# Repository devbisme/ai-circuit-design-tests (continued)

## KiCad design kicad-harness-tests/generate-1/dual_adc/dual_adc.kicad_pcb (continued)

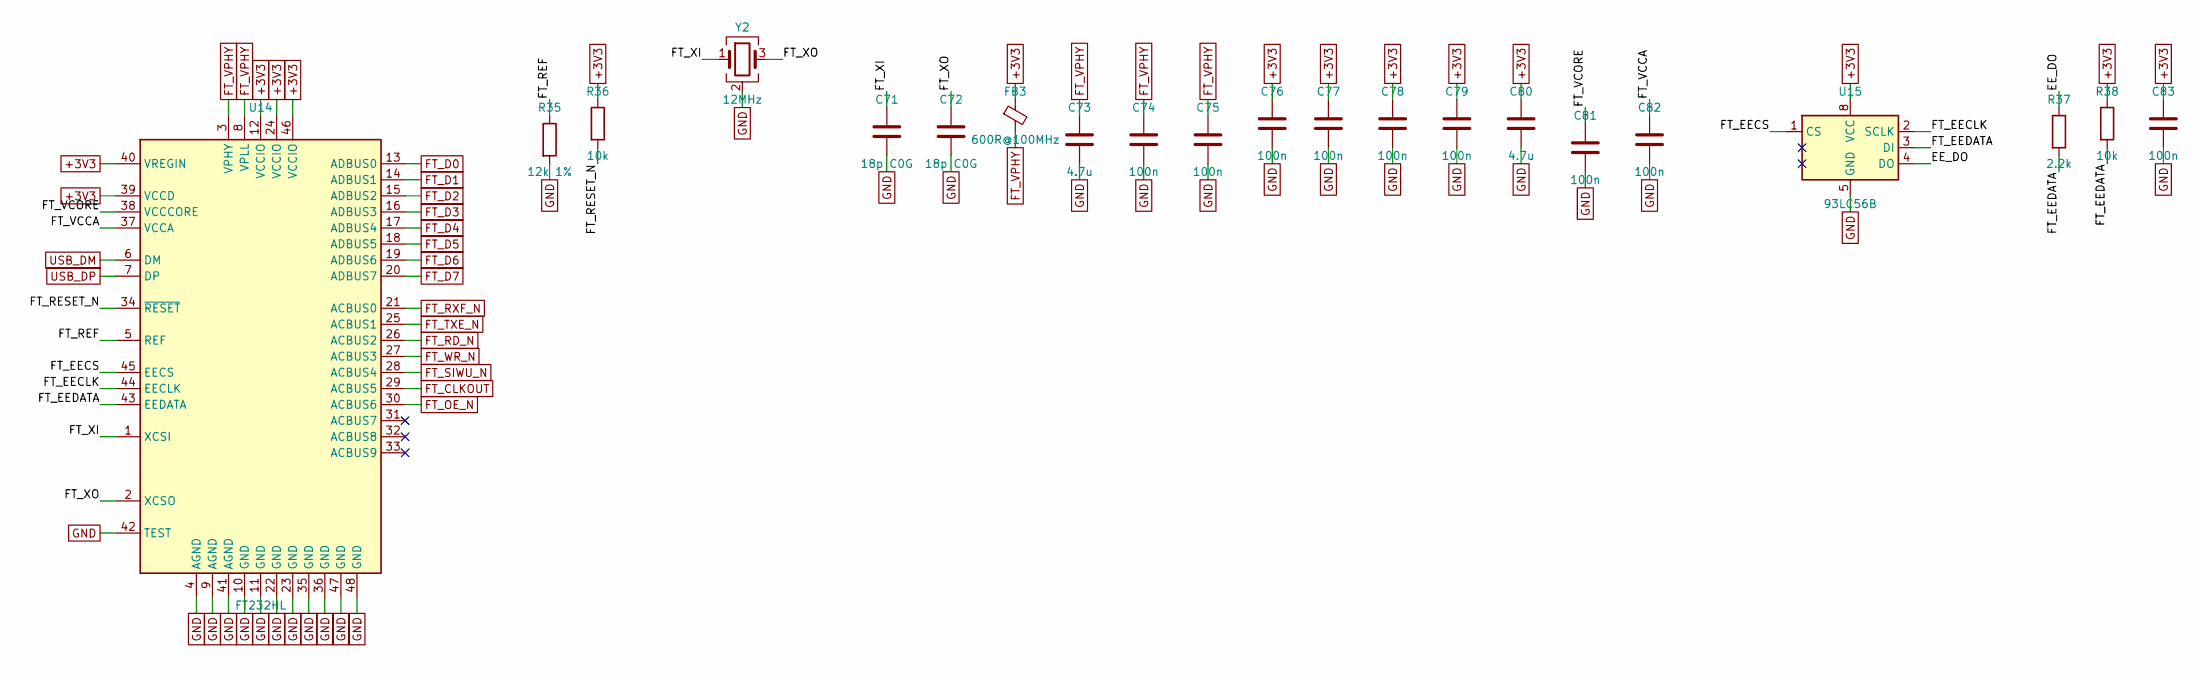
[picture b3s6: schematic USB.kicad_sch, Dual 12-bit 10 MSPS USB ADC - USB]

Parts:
C71, C72: 18p C0G; C_0603_1608Metric
C73, C80: 4.7u; C_0805_2012Metric
C74, C75, C76, C77, C78, C79, C81, C82, C83: 100n; C_0603_1608Metric
FB3: 600R@100MHz; L_0805_2012Metric
R35: 12k 1%; R_0603_1608Metric
R36, R38: 10k; R_0603_1608Metric
R37: 2.2k; R_0603_1608Metric
U14: FT232HL; LQFP-48_7x7mm_P0.5mm
U15: 93LC56B; SOIC-8_3.9x4.9mm_P1.27mm
Y2: 12MHz; Crystal_SMD_3225-4Pin_3.2x2.5mm

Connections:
+3V3: C76.1, C77.1, C78.1, C79.1, C80.1, C83.1, FB3.1, R36.1, R38.1, U14.12 (VCCIO), U14.24 (VCCIO), U14.39 (VCCD), U14.40 (VREGIN), U14.46 (VCCIO), U15.8 (VCC); also elsewhere on the board
/USB/EE_DO: R37.1, U15.4 (DO)
/USB/FT_EECLK: U14.44 (EECLK), U15.2 (SCLK)
/USB/FT_EECS: U14.45 (EECS), U15.1 (CS)
/USB/FT_EEDATA: R37.2, R38.2, U14.43 (EEDATA), U15.3 (DI)
/USB/FT_REF: R35.1, U14.5 (REF)
/USB/FT_RESET_N: R36.2, U14.34 (~RESET)
/USB/FT_VCCA: C82.1, U14.37 (VCCA)
/USB/FT_VCORE: C81.1, U14.38 (VCCCORE)
/USB/FT_XI: C71.1, U14.1 (XCSI), Y2.1
/USB/FT_XO: C72.1, U14.2 (XCSO), Y2.3
FT_CLKOUT: U14.29 (ACBUS5); also elsewhere on the board
FT_D0: U14.13 (ADBUS0); also elsewhere on the board
FT_D1: U14.14 (ADBUS1); also elsewhere on the board
FT_D2: U14.15 (ADBUS2); also elsewhere on the board
FT_D3: U14.16 (ADBUS3); also elsewhere on the board
FT_D4: U14.17 (ADBUS4); also elsewhere on the board
FT_D5: U14.18 (ADBUS5); also elsewhere on the board
FT_D6: U14.19 (ADBUS6); also elsewhere on the board
FT_D7: U14.20 (ADBUS7); also elsewhere on the board
FT_OE_N: U14.30 (ACBUS6); also elsewhere on the board
FT_RD_N: U14.26 (ACBUS2); also elsewhere on the board
FT_RXF_N: U14.21 (ACBUS0); also elsewhere on the board
FT_SIWU_N: U14.28 (ACBUS4); also elsewhere on the board
FT_TXE_N: U14.25 (ACBUS1); also elsewhere on the board
FT_VPHY: C73.1, C74.1, C75.1, FB3.2, U14.3 (VPHY), U14.8 (VPLL)
FT_WR_N: U14.27 (ACBUS3); also elsewhere on the board
GND: C71.2, C72.2, C73.2, C74.2, C75.2, C76.2, C77.2, C78.2, C79.2, C80.2, C81.2, C82.2, C83.2, R35.2, U14.4 (AGND), U14.9 (AGND), U14.10 (GND), U14.11 (GND), U14.22 (GND), U14.23 (GND), U14.35 (GND), U14.36 (GND), U14.41 (AGND), U14.42 (TEST), U14.47 (GND), U14.48 (GND), U15.5 (GND), Y2.2 (G), Y2.4 (G); also elsewhere on the board
USB_DM: U14.6 (DM); also elsewhere on the board
USB_DP: U14.7 (DP); also elsewhere on the board

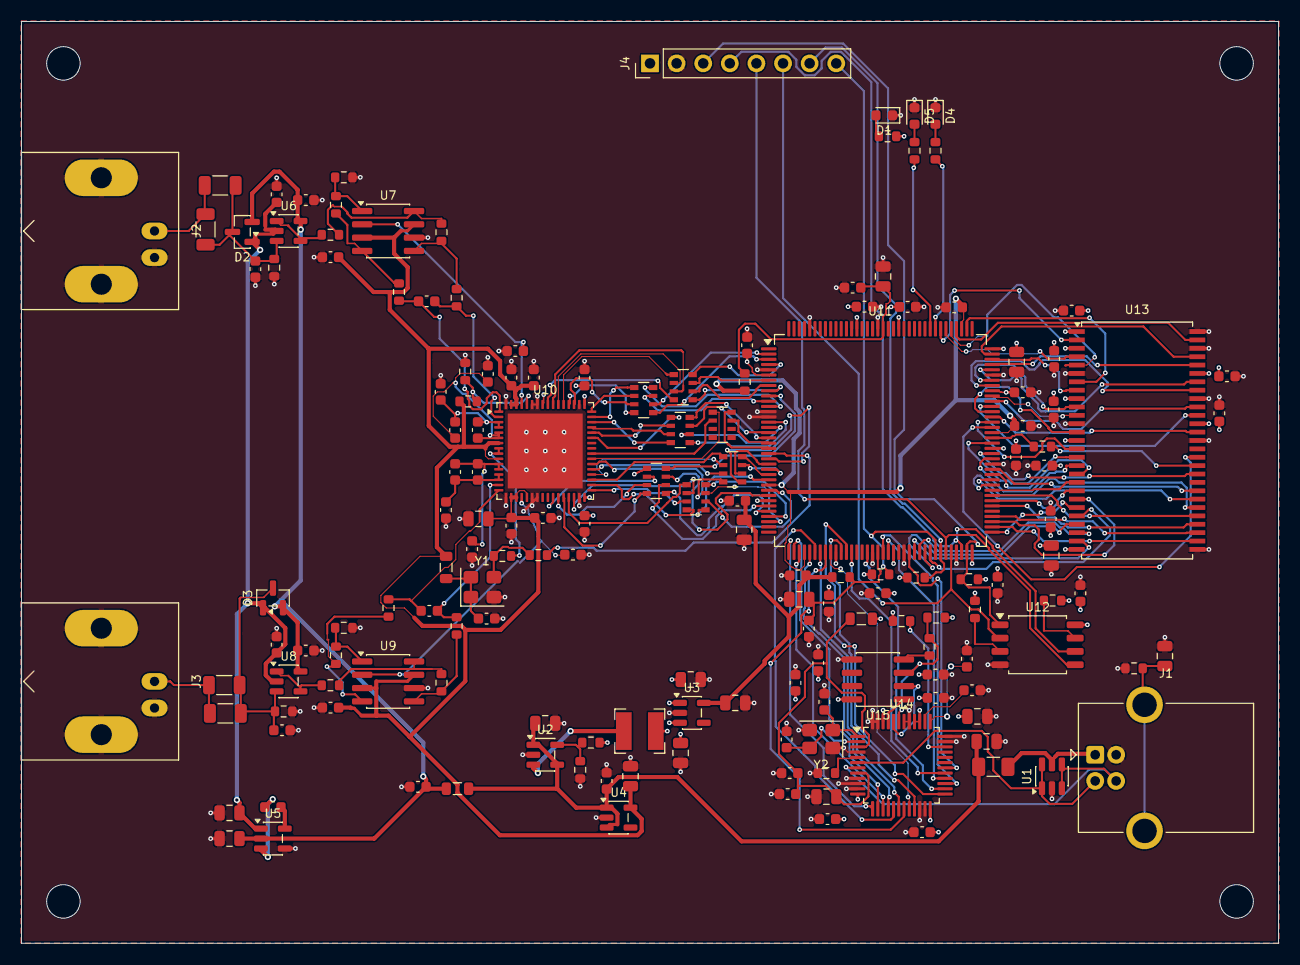
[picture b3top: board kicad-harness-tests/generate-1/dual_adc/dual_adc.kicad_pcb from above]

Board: 4 copper layers, 120.0 x 88.0 mm, 163 parts (0 on the bottom side), 176 nets.

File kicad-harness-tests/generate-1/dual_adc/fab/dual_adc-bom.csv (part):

"Refs","Value","Footprint","Qty","DNP"
"C1","4.7n","Capacitor_SMD:C_0805_2012Metric","1",""
"C2","10u","Capacitor_SMD:C_0805_2012Metric","1",""
"C3","10u","Capacitor_SMD:C_0805_2012Metric","1",""
"C4","22u","Capacitor_SMD:C_0805_2012Metric","1",""
"C5","22u","Capacitor_SMD:C_0805_2012Metric","1",""
"C6","1u","Capacitor_SMD:C_0603_1608Metric","1",""
"C7","10u","Capacitor_SMD:C_0805_2012Metric","1",""
"C8","1u","Capacitor_SMD:C_0603_1608Metric","1",""
"C9","10u","Capacitor_SMD:C_0805_2012Metric","1",""
"C10","10u","Capacitor_SMD:C_0805_2012Metric","1",""
"C11","1u","Capacitor_SMD:C_0603_1608Metric","1",""
"C12","1u","Capacitor_SMD:C_0603_1608Metric","1",""
"C13","4.7u","Capacitor_SMD:C_0805_2012Metric","1",""
"C14","16p C0G","Capacitor_SMD:C_1206_3216Metric","1",""
"C15","150p C0G","Capacitor_SMD:C_0603_1608Metric","1",""
"C16","100n","Capacitor_SMD:C_0603_1608Metric","1",""
"C17","100n","Capacitor_SMD:C_0603_1608Metric","1",""
"C18","100n","Capacitor_SMD:C_0603_1608Metric","1",""
"C19","330p C0G","Capacitor_SMD:C_0603_1608Metric","1",""
"C20","16p C0G","Capacitor_SMD:C_1206_3216Metric","1",""
"C21","150p C0G","Capacitor_SMD:C_0603_1608Metric","1",""
"C22","100n","Capacitor_SMD:C_0603_1608Metric","1",""
"C23","100n","Capacitor_SMD:C_0603_1608Metric","1",""
"C24","100n","Capacitor_SMD:C_0603_1608Metric","1",""
"C25","330p C0G","Capacitor_SMD:C_0603_1608Metric","1",""
"C26","100n","Capacitor_SMD:C_0603_1608Metric","1",""
"C27","100n","Capacitor_SMD:C_0603_1608Metric","1",""
"C28","100n","Capacitor_SMD:C_0603_1608Metric","1",""
"C29","100n","Capacitor_SMD:C_0603_1608Metric","1",""
"C30","10u","Capacitor_SMD:C_0805_2012Metric","1",""
"C31","100n","Capacitor_SMD:C_0603_1608Metric","1",""
"C32","100n","Capacitor_SMD:C_0603_1608Metric","1",""
"C33","100n","Capacitor_SMD:C_0603_1608Metric","1",""
"C34","2.2u","Capacitor_SMD:C_0603_1608Metric","1",""
"C35","1u","Capacitor_SMD:C_0603_1608Metric","1",""
"C36","1u","Capacitor_SMD:C_0603_1608Metric","1",""
"C37","2.2u","Capacitor_SMD:C_0603_1608Metric","1",""
"C38","100n","Capacitor_SMD:C_0603_1608Metric","1",""
"C39","2.2u","Capacitor_SMD:C_0603_1608Metric","1",""
"C40","1u","Capacitor_SMD:C_0603_1608Metric","1",""
"C41","1u","Capacitor_SMD:C_0603_1608Metric","1",""
"C42","2.2u","Capacitor_SMD:C_0603_1608Metric","1",""
"C43","100n","Capacitor_SMD:C_0603_1608Metric","1",""
"C44","100n","Capacitor_SMD:C_0603_1608Metric","1",""
"C45","100n","Capacitor_SMD:C_0603_1608Metric","1",""
"C46","100n","Capacitor_SMD:C_0603_1608Metric","1",""
"C47","100n","Capacitor_SMD:C_0603_1608Metric","1",""
"C48","10u","Capacitor_SMD:C_0805_2012Metric","1",""
"C49","100n","Capacitor_SMD:C_0603_1608Metric","1",""
"C50","100n","Capacitor_SMD:C_0603_1608Metric","1",""
"C51","100n","Capacitor_SMD:C_0603_1608Metric","1",""
"C52","100n","Capacitor_SMD:C_0603_1608Metric","1",""
"C53","100n","Capacitor_SMD:C_0603_1608Metric","1",""
"C54","100n","Capacitor_SMD:C_0603_1608Metric","1",""
"C55","100n","Capacitor_SMD:C_0603_1608Metric","1",""
"C56","100n","Capacitor_SMD:C_0603_1608Metric","1",""
"C57","10u","Capacitor_SMD:C_0805_2012Metric","1",""
"C58","10u","Capacitor_SMD:C_0805_2012Metric","1",""
"C59","100n","Capacitor_SMD:C_0603_1608Metric","1",""
"C60","10u","Capacitor_SMD:C_0805_2012Metric","1",""
"C61","100n","Capacitor_SMD:C_0603_1608Metric","1",""
"C62","100n","Capacitor_SMD:C_0603_1608Metric","1",""
"C63","100n","Capacitor_SMD:C_0603_1608Metric","1",""
"C64","100n","Capacitor_SMD:C_0603_1608Metric","1",""
"C65","100n","Capacitor_SMD:C_0603_1608Metric","1",""
"C66","100n","Capacitor_SMD:C_0603_1608Metric","1",""
"C67","100n","Capacitor_SMD:C_0603_1608Metric","1",""
"C68","100n","Capacitor_SMD:C_0603_1608Metric","1",""
"C69","100n","Capacitor_SMD:C_0603_1608Metric","1",""
"C70","10u","Capacitor_SMD:C_0805_2012Metric","1",""
"C71","18p C0G","Capacitor_SMD:C_0603_1608Metric","1",""
"C72","18p C0G","Capacitor_SMD:C_0603_1608Metric","1",""
"C73","4.7u","Capacitor_SMD:C_0805_2012Metric","1",""
"C74","100n","Capacitor_SMD:C_0603_1608Metric","1",""
"C75","100n","Capacitor_SMD:C_0603_1608Metric","1",""
"C76","100n","Capacitor_SMD:C_0603_1608Metric","1",""
"C77","100n","Capacitor_SMD:C_0603_1608Metric","1",""
"C78","100n","Capacitor_SMD:C_0603_1608Metric","1",""
"C79","100n","Capacitor_SMD:C_0603_1608Metric","1",""
"C80","4.7u","Capacitor_SMD:C_0805_2012Metric","1",""
"C81","100n","Capacitor_SMD:C_0603_1608Metric","1",""
"C82","100n","Capacitor_SMD:C_0603_1608Metric","1",""
"C83","100n","Capacitor_SMD:C_0603_1608Metric","1",""
"D1","green","LED_SMD:LED_0603_1608Metric","1",""
"D2","BAV99","Package_TO_SOT_SMD:SOT-23","1",""
"D3","BAV99","Package_TO_SOT_SMD:SOT-23","1",""
"D4","yellow","LED_SMD:LED_0603_1608Metric","1",""
"D5","yellow","LED_SMD:LED_0603_1608Metric","1",""
"F1","750mA hold","Fuse:Fuse_1206_3216Metric","1",""
"FB1","600R@100MHz","Inductor_SMD:L_0805_2012Metric","1",""
"FB2","600R@100MHz","Inductor_SMD:L_0805_2012Metric","1",""
"FB3","600R@100MHz","Inductor_SMD:L_0805_2012Metric","1",""
"H1","MountingHole","MountingHole:MountingHole_3.2mm_M3","1",""
"H2","MountingHole","MountingHole:MountingHole_3.2mm_M3","1",""
"H3","MountingHole","MountingHole:MountingHole_3.2mm_M3","1",""
"H4","MountingHole","MountingHole:MountingHole_3.2mm_M3","1",""
"J1","USB_B","Connector_USB:USB_B_OST_USB-B1HSxx_Horizontal","1",""
"J2","BNC_CHA","Connector_Coaxial:BNC_Amphenol_B6252HB-NPP3G-50_Horizontal","1",""
"J3","BNC_CHB","Connector_Coaxial:BNC_Amphenol_B6252HB-NPP3G-50_Horizontal","1",""
"J4","PROG","Connector_PinHeader_2.54mm:PinHeader_1x08_P2.54mm_Vertical","1",""
"L1","2.2u","Inductor_SMD:L_Bourns-SRN4018","1",""
"R1","1M","Resistor_SMD:R_0603_1608Metric","1",""
"R2","100k","Resistor_SMD:R_0603_1608Metric","1",""
"R3","22.1k","Resistor_SMD:R_0603_1608Metric","1",""
"R4","1k","Resistor_SMD:R_0603_1608Metric","1",""
"R5","909k","Resistor_SMD:R_1206_3216Metric","1",""
"R6","100k","Resistor_SMD:R_0603_1608Metric","1",""
"R7","1k","Resistor_SMD:R_0603_1608Metric","1",""
"R8","1k","Resistor_SMD:R_0603_1608Metric","1",""
"R9","953","Resistor_SMD:R_0603_1608Metric","1",""
"R10","953","Resistor_SMD:R_0603_1608Metric","1",""
"R11","49.9","Resistor_SMD:R_0603_1608Metric","1",""
"R12","49.9","Resistor_SMD:R_0603_1608Metric","1",""
"R13","909k","Resistor_SMD:R_1206_3216Metric","1",""
"R14","100k","Resistor_SMD:R_0603_1608Metric","1",""
"R15","1k","Resistor_SMD:R_0603_1608Metric","1",""
"R16","1k","Resistor_SMD:R_0603_1608Metric","1",""
"R17","953","Resistor_SMD:R_0603_1608Metric","1",""
"R18","953","Resistor_SMD:R_0603_1608Metric","1",""
"R19","49.9","Resistor_SMD:R_0603_1608Metric","1",""
"R20","49.9","Resistor_SMD:R_0603_1608Metric","1",""
"R21","10k","Resistor_SMD:R_0603_1608Metric","1",""
"R22","20k","Resistor_SMD:R_0603_1608Metric","1",""
"R23","33","Resistor_SMD:R_0603_1608Metric","1",""
"R24","33","Resistor_SMD:R_0603_1608Metric","1",""
"R25","100","Resistor_SMD:R_0603_1608Metric","1",""
"R26","100","Resistor_SMD:R_0603_1608Metric","1",""
"R27","10k","Resistor_SMD:R_0603_1608Metric","1",""
"R28","10k","Resistor_SMD:R_0603_1608Metric","1",""
"R29","10k","Resistor_SMD:R_0603_1608Metric","1",""
"R30","10k","Resistor_SMD:R_0603_1608Metric","1",""
"R31","10k","Resistor_SMD:R_0603_1608Metric","1",""
"R32","1k","Resistor_SMD:R_0603_1608Metric","1",""
"R33","1k","Resistor_SMD:R_0603_1608Metric","1",""
"R34","22","Resistor_SMD:R_0603_1608Metric","1",""
"R35","12k 1%","Resistor_SMD:R_0603_1608Metric","1",""
"R36","10k","Resistor_SMD:R_0603_1608Metric","1",""
"R37","2.2k","Resistor_SMD:R_0603_1608Metric","1",""
"R38","10k","Resistor_SMD:R_0603_1608Metric","1",""
"RN1","4x33","Resistor_SMD:R_Array_Convex_4x0603","1",""
"RN2","4x33","Resistor_SMD:R_Array_Convex_4x0603","1",""
"RN3","4x33","Resistor_SMD:R_Array_Convex_4x0603","1",""
"RN4","4x33","Resistor_SMD:R_Array_Convex_4x0603","1",""
"RN5","4x33","Resistor_SMD:R_Array_Convex_4x0603","1",""
"RN6","4x33","Resistor_SMD:R_Array_Convex_4x0603","1",""
"RN7","4x33","Resistor_SMD:R_Array_Convex_4x0603","1",""
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
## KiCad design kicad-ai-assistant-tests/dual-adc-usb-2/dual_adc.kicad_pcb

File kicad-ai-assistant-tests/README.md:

# KiCad-AI-Assistant — tests

## Tool under test

[KiCad-AI-Assistant](https://github.com/paul356/KiCad-AI-Assistant) has two parts:

- **A KiCad action plugin.** It is a chat panel in the PCB editor with its own agent loop and a
  Freerouting integration.
- **An MCP server, `kcaa`.** It runs standalone with the "full" profile and registers 129
  tools for:
  - Schematic editing: symbol search and placement, wires, labels, no-connects, sheets and
    sheet pins, properties, symbol and library creation, group placement.
  - Schematic analysis: netlist extraction, ERC through `kicad-cli`, circuit-pattern
    recognition, BOM analysis, validation.
  - PCB editing: footprint search and placement, alignment and distribution, flipping,
    groups, board outline, zones, net classes and design rules.
  - Routing: a pad-to-pad push-and-shove router, vias, a ratsnest query, and a pure-Python
    board renderer.
  - Live-KiCad (IPC) actions: update the PCB from the schematic, refill zones, save, reload,
    and open the DRC dialog.
  - Twelve Markdown "skills" with workflow guidance.

Claude Code used only the MCP server; the plugin's chat panel was not used. Schematic tools edit
`.kicad_sch` files directly (via `kicad-skip`); the IPC tools need the KiCad GUI open with its
API server enabled. Installation is described in [`setup.md`](setup.md).

The tool is a hybrid (both analyzer and generator), so it was tested in both roles, like
[kicad-mcp-server](../kicad-mcp-server-tests/), [kicad-mcp-pro](../kicad-mcp-pro-tests/) and
[eda-agent](../eda-agent-tests/).

- **Version:** kcaa 0.2.7 from PyPI. Plugin files are from the repo at commit ce4161f
  (2026-10-09).
- **Profile:** `full` (standalone MCP server, stdio).
- **Model:** Claude Opus 5.5 on a Claude Pro plan, Claude Code v2.1.296 (both runs).
- **Backend:** KiCad 10.0.4 (`~/bin/kicad10-root`: `kicad-cli`, pcbnew Python, and the GUI for
  IPC). Run 2 also used Freerouting 2.4.1.

## Why this tool

- It is one of the few KiCad MCP servers with tools for both schematic capture **and** PCB
  work: placement, zones, rules and its own router.
- It ships workflow skills and a placement scorer, which suggest it is aimed at building
  designs, not only inspecting them.

## Runs

| Run | What it tests | Prompts | Outcome | Equiv. API cost | Time |
|---|---|---|---|---|---|
| [`dual-adc-usb-1`](dual-adc-usb-1/) | **Analysis** and JLCPCB fab outputs for an existing design | 1 (multi-part, [`analysis_prompt.txt`](dual-adc-usb-1/analysis_prompt.txt)) | ERC 0 errors, DRC 0 errors; 18 ranked findings; Gerbers, BOM, CPL, PNG. Most of the review came from fallbacks because kcaa's analysis tools failed on this design | $3.71 | ~20 min |
| [`dual-adc-usb-2`](dual-adc-usb-2/) | A **full design**, from requirements to Gerbers | 1, plus "keep going" after a usage-limit stop | 6-sheet schematic and routed 4-layer board. ERC 0 errors, DRC 0 errors / 0 unconnected / 0 parity | $19.38 | ~3h45m wall clock, including a usage-limit pause and two ~36-minute Freerouting runs |

Each run directory has an `executive_summary.md`; start there. Costs are the equivalent
first-party API price of the tokens used (`claude_cost.txt`), not what the Pro subscription
billed. I have not yet validated the findings in either run myself.

### dual-adc-usb-1: analyzer on an existing design

The input is the KiCad project produced by
[Konnect run 2](../konnect-tests/dual-adc-usb-2/): a 4-layer, 140 × 90 mm dual-channel 12-bit,
10 MS/s ADC board with a USB 2.0 interface (LTC2290 ADC, iCE40HX4K FPGA, SDRAM, FT2232HL).
The `.kicad_*` files are unchanged copies; the run checked their md5 sums before and after.
kicad-happy run 1, kicad-mcp-server run 1, kicad-mcp-pro run 1 and eda-agent run 1 analyzed
the same design.

Prompt ([`analysis_prompt.txt`](dual-adc-usb-1/analysis_prompt.txt)):

```
Analyze the kicad project in this directory using KiCad-AI-Assistant (kcaa). A KiCad 10
executable is in /home/devb/bin/kicad10.

Review the design for architectural, physical design, and manufacturing problems.

Output gerber files for jlcpcb.

Generate the BOM and pick-and-place files for JLCPCB

Create a PNG of the PCB showing the front and back traces, footprints, and
silkscreen along with the board edges all on a dark-gray background.

Write an executive_summary.md file explaining what you did and what results were
found for this kicad project.
```

Quick look:

- **Checks:** kcaa `run_erc` gave 0 errors. 201 of its 203 warnings are a global
  library-table artifact, not design problems. DRC via `kicad-cli`: 0 errors, 0 unconnected,
  343 warnings.
- **Findings (18, ranked):**
  - Architectural: the FPGA has no clock before enumeration, and the ADC can be back-powered
    while its rail is gated; the FDA output can overdrive the ADC inputs; USB throughput is
    marginal for streaming.
  - Decoupling far from IC pins (up to 22 mm).
  - Anti-alias caps 15–18 mm from the ADC.
  - Asymmetric differential paths; USB D+/D− not routed as a pair.
  - Two verified datasheet deviations (LM27762).
  - Silkscreen and BOM/assembly issues.
- **Datasheets:** the two that downloaded were read. The LTC2290 and FT2232H downloads failed,
  so claims about those parts are from memory and are labelled that way.
- **kcaa's analysis tools were mostly wrong or empty on this label-connected hierarchical
  design:**
  - `extract_schematic_netlist` returned no pins.
  - `find_component_connections` and `identify_circuit_patterns` see one sheet at a time, and
    their pattern guesses were often wrong.
  - `get_ratsnest` gave false "unconnected" results; `get_board_info` reported 0 copper
    layers.
  - `export_bom_csv` runs the system KiCad 9 `kicad-cli`.
  - There is no headless DRC.
- **Fallbacks:** the review relied on `kicad-cli`, a netlist pin-map script, a pcbnew geometry
  script and datasheets. Fab outputs were also made with `kicad-cli`.
- The transcript is at `dual-adc-usb-1/reports/claude_transcript.txt`.

### dual-adc-usb-2: full design

The prompt is [`dual-adc-prompt.txt`](dual-adc-usb-2/dual-adc-prompt.txt). It is identical to
the one used for the other tools' run 2.

Prompts, in sequence in one session:

```
create the design described in dual-adc-prompt.txt.
```
```
keep going
```

Claude stopped once at the Pro plan's usage limit, after the board had been placed. When the
limit reset, Claude resumed on its own. The second prompt was given while it was waiting on
Freerouting.

Quick look:

- **Design:**
  - Signal path: BNC → 1.009 MΩ ‖ 13.5 pF compensated 10:1 attenuator → BAV99 clamp →
    OPA810 → THS4521 (2-pole MFB plus an output RC pole, about 3rd-order Butterworth at
    3.2 MHz) → LTC2290.
  - Capture and link: iCE40HX4K with 32 MB SDRAM (1.6 s of capture); FT232H in synchronous
    FIFO mode.
  - Power: USB-B, about 265 mA estimated.
  - Decisions with options are in [`design_notes.md`](dual-adc-usb-2/design_notes.md).
- **Schematic:** 6 sheets, 182 parts, 160 nets.
  - Built with about 2,500 kcaa tool calls (placement, rename, stub wires, labels, power
    symbols, no-connects, properties), all driven from one netlist file
    (`scripts/design.py`). The calls were made in-process through `scripts/kcaa_call.py`,
    which runs the same code as the MCP server.
  - The kicad-cli netlist matches `design.py` exactly. ERC: 0 errors, 2 benign warnings.
  - The schematic can be rebuilt end to end from the scripts.
- **PCB:** 128 × 85 mm, 4 layers: In1 solid GND, In2 split between +3V3 (digital) and GND
  (analog), decoupling caps on B.Cu.
  - kcaa did the update from the schematic (0 warnings), footprint positioning with its
    collision guard, flips, net classes and rules, and renders.
  - Claude's scripts did placement planning, the locked plane fanout and Freerouting
    DSN/SES. Freerouting left 5 connections unrouted, but they were all complete after the
    SES import.
  - DRC: 0 errors, 0 unconnected, 0 parity issues. 147 warnings, all silkscreen.
- **kcaa gaps found** (12, all worked around):
  - Environment and index: `KICAD_SYMBOL_DIR` from the shell profile overrides kcaa's KiCad 10
    symbol path, so the index came up empty. Tools that log through `ctx.info` crash
    in-process.
  - Symbol tools: `get_symbol_pins` returns 0 pins for derived symbols. Private `KLC_*`
    properties are copied without their value, so KiCad can't open the sheet.
  - Schematic structure: child-sheet instance paths and page numbers are wrong;
    `rename_symbol` needs a uuid that `extract_schematic_netlist` doesn't return; extra units
    land off-grid; 180°/270° labels get the wrong justification; symbols are moved off
    existing wires.
  - PCB: `update_pcb_from_schematic` needs the KiCad project manager plus a click in the
    dialog (done here with xdotool); `flip_footprint` leaves the courtyard on F.CrtYd and
    doesn't mirror text.
  - Routing: there is no autorouter in the MCP server, and the plugin's Freerouting jar needs
    Java 25.
- **Self-inflicted problem, fixed:** a pcbnew `SaveBoard` from a directory with no
  `.kicad_pro` reset the project's rules to defaults. The project file was restored from
  kcaa's backup.
- **Not ready for fab:**
  - Anti-aliasing at 10 Msps is weak (−29 dB at 10 MHz); the upgrade path is the
    pin-compatible LTC2292 with decimation.
  - Pin wiring written from memory needs a datasheet check: FT232H VCCD/VPHY/VPLL, THS4521
    output polarity, LTC2290 strapping, iCE40 VPP_FAST.
  - VBUS capacitance is about 15 µF, above USB's 10 µF guideline.
  - Silkscreen needs cleanup; there are no MPN/LCSC fields.

## Layout

```
kicad-ai-assistant-tests/
├── README.md                   <- this file
├── setup.md                    <- how KiCad-AI-Assistant / kcaa was installed and configured
├── dual-adc-usb-1/             <- run 1: analysis of the Konnect run-2 design
│   ├── executive_summary.md    <- start here
│   ├── analysis_prompt.txt     <- the prompt
│   ├── claude_cost.txt         <- token usage and equivalent API cost
│   ├── session_cost.py         <- script that produced claude_cost.txt
│   ├── dual_adc_usb.kicad_pro, .kicad_pcb, .kicad_dru, .kicad_prl, .kicad_sch
│   ├── afe_a, afe_b, adc, fpga, usb, power .kicad_sch
│   ├── dual_adc_usb_pcb.png    <- PCB render on a dark-gray background
│   ├── jlcpcb/                 <- Gerber zip, unzipped gerbers, JLC BOM/CPL, THT list
│   └── reports/                <- claude_transcript.txt, kcaa ERC, DRC+parity JSON, netlist,
│                                  pinmap.txt, pcb_geometry.txt, raw BOM/pos, scripts/
└── dual-adc-usb-2/             <- run 2: full design from the dual-ADC prompt
    ├── executive_summary.md    <- start here
    ├── design_notes.md         <- requirements, budgets, decisions with options, risks
    ├── dual-adc-prompt.txt     <- the design prompt
    ├── claude_transcript.txt   <- session transcript (/export)
    ├── claude_cost.txt         <- token usage and equivalent API cost
    ├── session_cost.py         <- script that produced claude_cost.txt
    ├── dual_adc.kicad_pro, .kicad_pcb, .kicad_prl, .kicad_sch (root)
    ├── power, frontend, adc, fpga, sdram, usb .kicad_sch
    ├── *.bak, dual_adc-backups/ <- backups written by kcaa and KiCad
    ├── sym-lib-table, fp-lib-table, lib/dual_adc.kicad_sym  <- project libraries
    │                              (flattened symbols; global tables were stale)
    ├── dual_adc_bom.csv        <- grouped BOM from design.py
    ├── fab/                    <- Gerbers, drill, pick-and-place, KiCad BOM
    ├── reports/                <- drc.rpt, erc.rpt, netlist_check.txt, schematic PDF,
    │                              pcb_top.pdf, pcb_render.png (kcaa renderer)
    ├── routing/                <- DSN, SES, Freerouting logs, intermediate boards, DRC runs
    └── scripts/
        ├── kcaa_call.py        <- calls kcaa tools in-process (env fix, ctx.info patch)
        ├── design.py           <- the netlist: parts, values, footprints, pin->net
        ├── filter_design.py    <- attenuator and anti-alias filter calculations
        ├── flatten_symbols.py  <- project library without `extends` / private properties
        ├── build_schematic.py  <- builds all sheets with kcaa tools (+ unit snap, label fix)
        ├── fix_hierarchy.py    <- fixes kcaa's child-sheet instance paths and page numbers
        ├── verify_netlist.py   <- kicad-cli netlist vs design.py
        ├── pins.py, sexp.py    <- pin dump via kcaa; small S-expression reader/writer
        ├── dump_fp.py, place_pcb.py  <- footprint geometry; placement plan applied with kcaa
        ├── fanout.py           <- locked GND/+3V3 plane fanout
        ├── fix_flips.py        <- repairs kcaa flip_footprint artifacts
        ├── zones.py            <- inner-layer plane zones
        ├── export_dsn.py, import_ses.py  <- Freerouting round trip
        └── make_bom.py         <- grouped BOM
```

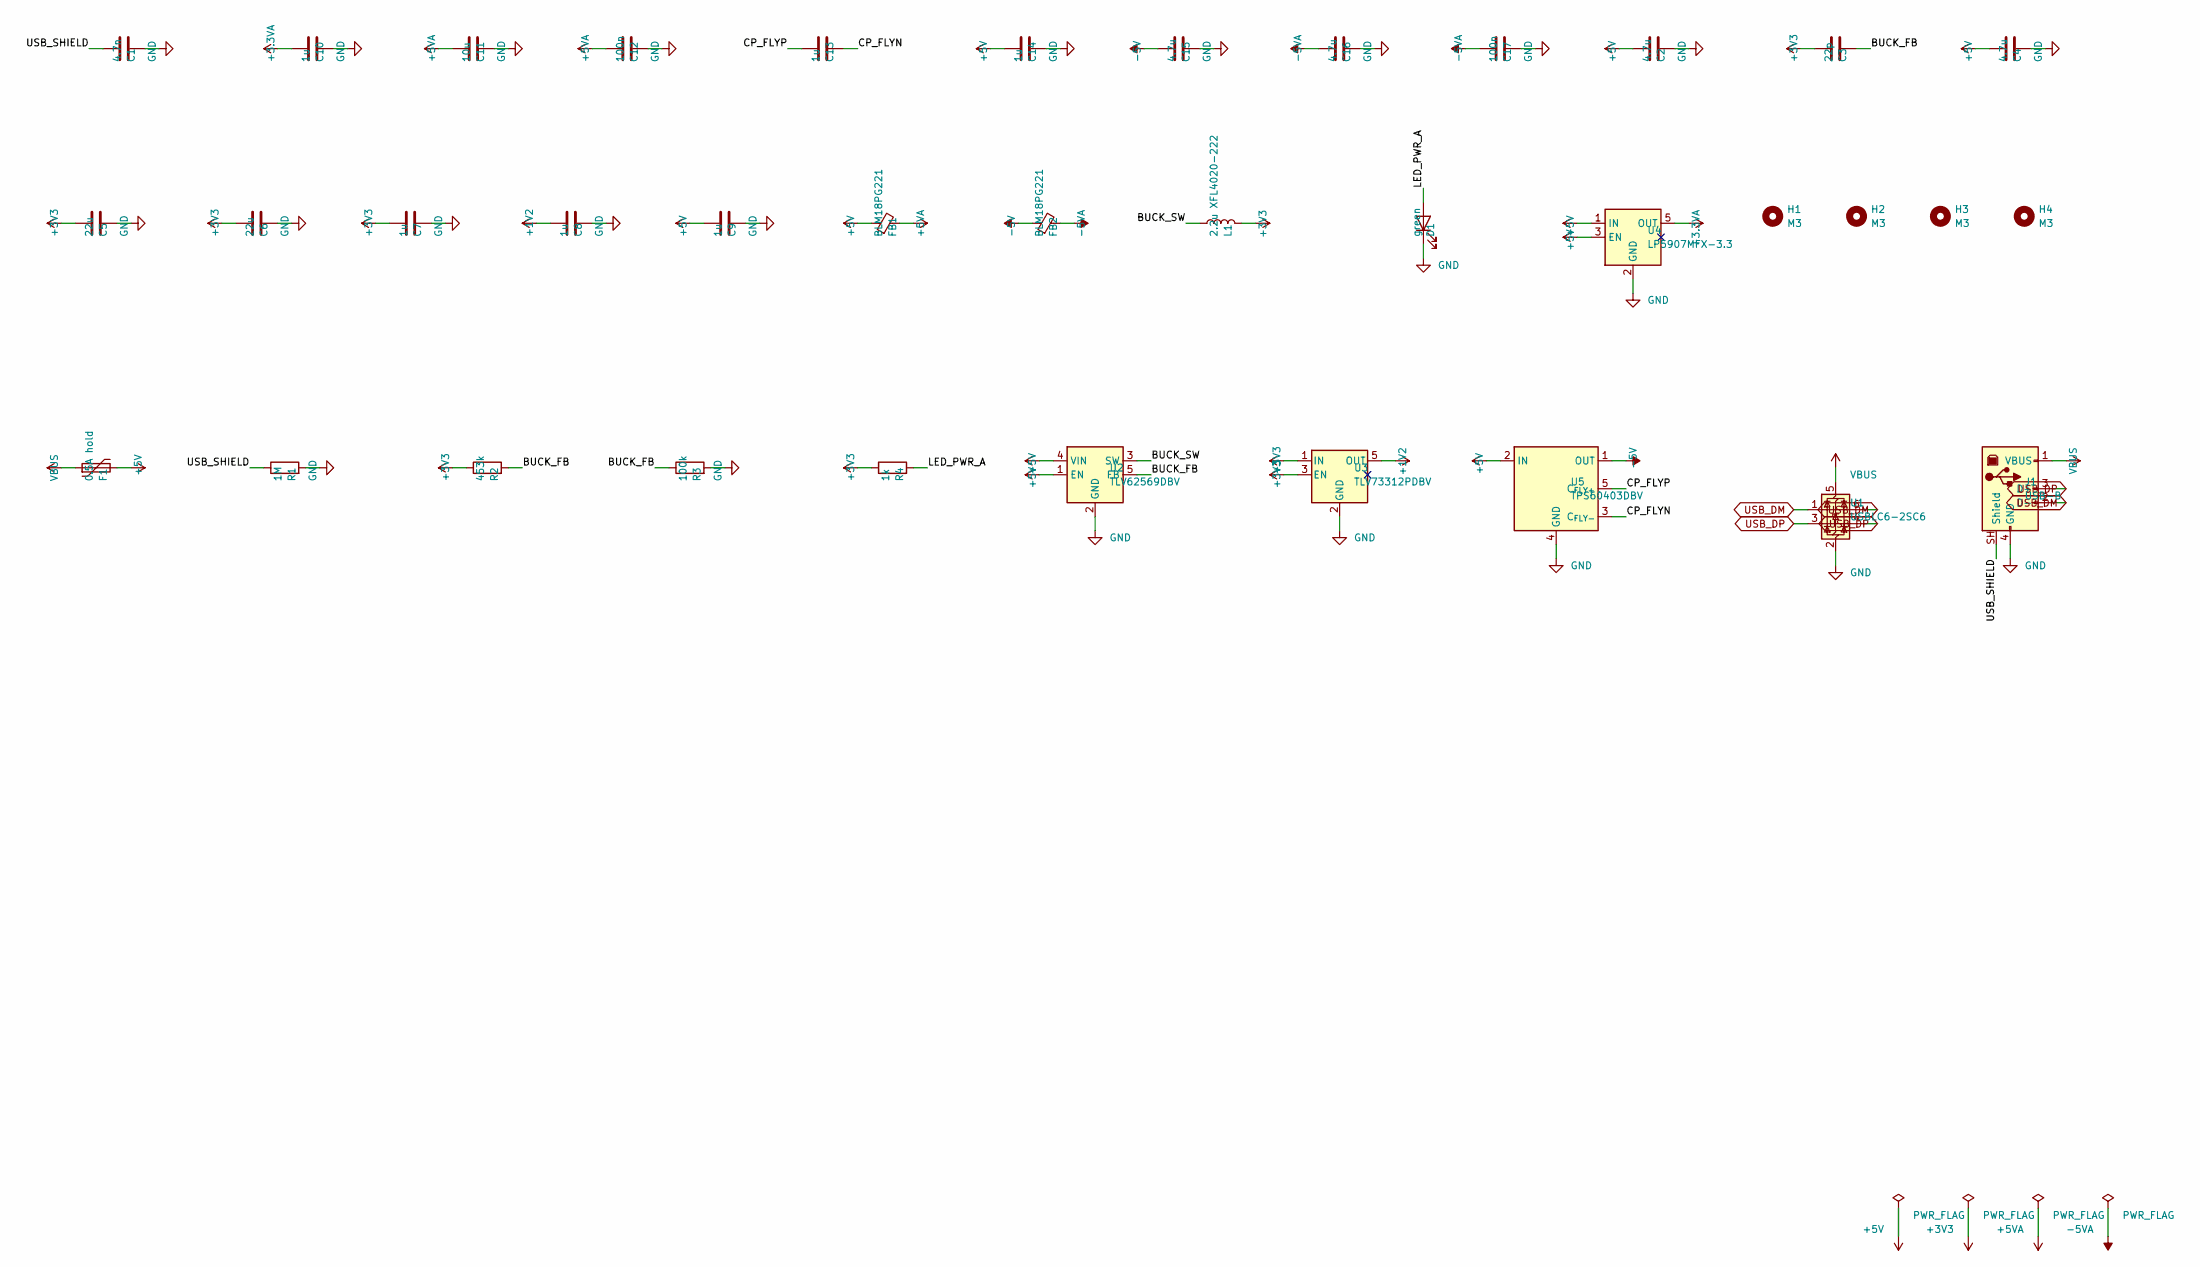
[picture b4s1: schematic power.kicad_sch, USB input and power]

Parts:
C1: 4.7n; C_0603_1608Metric
C2, C4, C15, C16: 4.7u; C_0805_2012Metric
C3: 22p; C_0603_1608Metric
C5, C6: 22u; C_0805_2012Metric
C7, C8, C9, C10, C13, C14: 1u; C_0603_1608Metric
C11: 10u; C_0805_2012Metric
C12, C17: 100n; C_0603_1608Metric
D1: green; LED_0603_1608Metric
F1: 0.5A hold; Fuse_1206_3216Metric
FB1, FB2: BLM18PG221; L_0603_1608Metric
H1, H2, H3, H4: M3; MountingHole_3.2mm_M3
J1: USB-B; USB_B_OST_USB-B1HSxx_Horizontal
L1: 2.2u XFL4020-222; L_Coilcraft_XxL4020
R1: 1M; R_0603_1608Metric
R2: 453k; R_0603_1608Metric
R3: 100k; R_0603_1608Metric
R4: 1k; R_0603_1608Metric
U1: USBLC6-2SC6; SOT-23-6
U2: TLV62569DBV; SOT-23-5
U3: TLV73312PDBV; SOT-23-5
U4: LP5907MFX-3.3; SOT-23-5
U5: TPS60403DBV; SOT-23-5

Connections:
+1V2: C8.1, U3.5 (OUT); also elsewhere on the board
+3.3VA: C10.1, U4.5 (OUT); also elsewhere on the board
+3V3: C3.1, C5.1, C6.1, C7.1, L1.2, R2.1, R4.1, U3.1 (IN), U3.3 (EN); also elsewhere on the board
+5V: C2.1, C4.1, C9.1, C14.1, F1.2, FB1.1, U2.1 (EN), U2.4 (VIN), U4.1 (IN), U4.3 (EN), U5.2 (IN); also elsewhere on the board
+5VA: C11.1, C12.1, FB1.2; also elsewhere on the board
-5V: C15.1, FB2.1, U5.1 (OUT)
-5VA: C16.1, C17.1, FB2.2; also elsewhere on the board
/USB input and power/BUCK_FB: C3.2, R2.2, R3.1, U2.5 (FB)
/USB input and power/BUCK_SW: L1.1, U2.3 (SW)
/USB input and power/CP_FLYN: C13.2, U5.3 (C_{FLY-})
/USB input and power/CP_FLYP: C13.1, U5.5 (C_{FLY+})
/USB input and power/LED_PWR_A: D1.2 (A), R4.2
/USB input and power/USB_SHIELD: C1.1, J1.SH (Shield), R1.1
GND: C1.2, C2.2, C4.2, C5.2, C6.2, C7.2, C8.2, C9.2, C10.2, C11.2, C12.2, C14.2, C15.2, C16.2, C17.2, D1.1 (K), J1.4 (GND), R1.2, R3.2, U1.2 (GND), U2.2 (GND), U3.2 (GND), U4.2 (GND), U5.4 (GND); also elsewhere on the board
USB_DM: J1.2 (D-), U1.1 (I/O1), U1.6 (I/O1); also elsewhere on the board
USB_DP: J1.3 (D+), U1.3 (I/O2), U1.4 (I/O2); also elsewhere on the board
VBUS: F1.1, J1.1 (VBUS), U1.5 (VBUS)

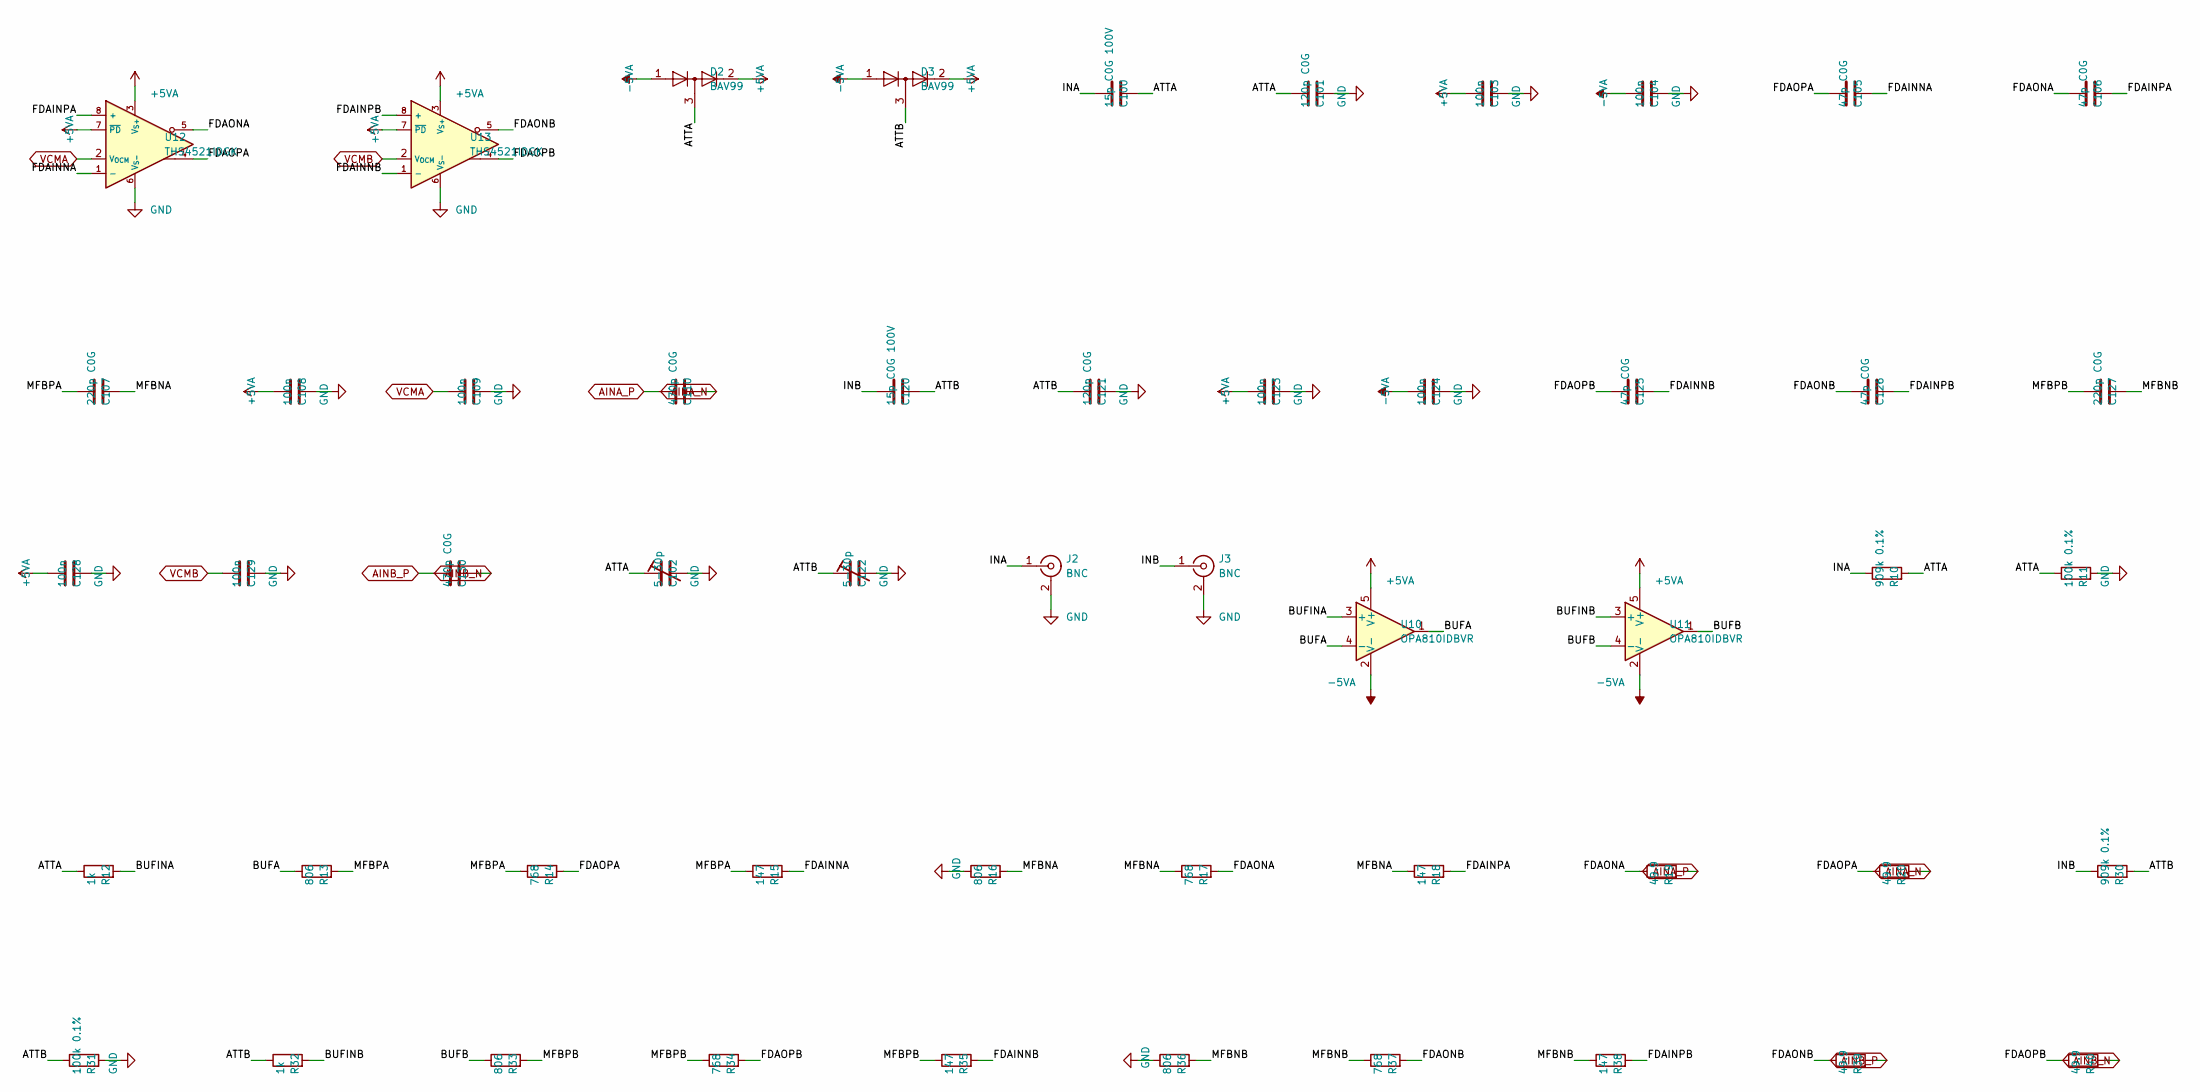
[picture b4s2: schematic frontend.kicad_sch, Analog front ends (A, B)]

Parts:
C100, C120: 15p C0G 100V; C_0805_2012Metric
C101, C121: 120p C0G; C_0603_1608Metric
C102, C122: 5-30p; C_Trimmer_Murata_TZC3
C103, C104, C108, C109, C123, C124, C128, C129: 100n; C_0603_1608Metric
C105, C106, C125, C126: 47p C0G; C_0603_1608Metric
C107, C127: 220p C0G; C_0603_1608Metric
C110, C130: 470p C0G; C_0603_1608Metric
D2, D3: BAV99; SOT-23
J2, J3: BNC; BNC_Amphenol_B6252HB-NPP3G-50_Horizontal
R10, R30: 909k 0.1%; R_1206_3216Metric
R11, R31: 100k 0.1%; R_0603_1608Metric
R12, R32: 1k; R_0603_1608Metric
R13, R16, R33, R36: 806; R_0603_1608Metric
R14, R17, R34, R37: 768; R_0603_1608Metric
R15, R18, R35, R38: 147; R_0603_1608Metric
R19, R20, R39, R40: 49.9; R_0603_1608Metric
U10, U11: OPA810IDBVR; SOT-23-5
U12, U13: THS4521IDGK; VSSOP-8_3x3mm_P0.65mm

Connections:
+5VA: C103.1, C108.1, C123.1, C128.1, D2.2 (A), D3.2 (A), U10.5 (V+), U11.5 (V+), U12.3 (V_{S+}), U12.7 (~PD), U13.3 (V_{S+}), U13.7 (~PD); also elsewhere on the board
-5VA: C104.1, C124.1, D2.1 (K), D3.1 (K), U10.2 (V-), U11.2 (V-); also elsewhere on the board
/Analog front ends (A, B)/ATTA: C100.2, C101.1, C102.1, D2.3 (K), R10.2, R11.1, R12.1
/Analog front ends (A, B)/ATTB: C120.2, C121.1, C122.1, D3.3 (K), R30.2, R31.1, R32.1
/Analog front ends (A, B)/BUFA: R13.1, U10.1, U10.4 (-)
/Analog front ends (A, B)/BUFB: R33.1, U11.1, U11.4 (-)
/Analog front ends (A, B)/BUFINA: R12.2, U10.3 (+)
/Analog front ends (A, B)/BUFINB: R32.2, U11.3 (+)
/Analog front ends (A, B)/FDAINNA: C105.2, R15.2, U12.1 (-)
/Analog front ends (A, B)/FDAINNB: C125.2, R35.2, U13.1 (-)
/Analog front ends (A, B)/FDAINPA: C106.2, R18.2, U12.8 (+)
/Analog front ends (A, B)/FDAINPB: C126.2, R38.2, U13.8 (+)
/Analog front ends (A, B)/FDAONA: C106.1, R17.2, R19.1, U12.5
/Analog front ends (A, B)/FDAONB: C126.1, R37.2, R39.1, U13.5
/Analog front ends (A, B)/FDAOPA: C105.1, R14.2, R20.1, U12.4
/Analog front ends (A, B)/FDAOPB: C125.1, R34.2, R40.1, U13.4
/Analog front ends (A, B)/INA: C100.1, J2.1 (In), R10.1
/Analog front ends (A, B)/INB: C120.1, J3.1 (In), R30.1
/Analog front ends (A, B)/MFBNA: C107.2, R16.2, R17.1, R18.1
/Analog front ends (A, B)/MFBNB: C127.2, R36.2, R37.1, R38.1
/Analog front ends (A, B)/MFBPA: C107.1, R13.2, R14.1, R15.1
/Analog front ends (A, B)/MFBPB: C127.1, R33.2, R34.1, R35.1
AINA_N: C110.2, R20.2; also elsewhere on the board
AINA_P: C110.1, R19.2; also elsewhere on the board
AINB_N: C130.2, R40.2; also elsewhere on the board
AINB_P: C130.1, R39.2; also elsewhere on the board
GND: C101.2, C102.2, C103.2, C104.2, C108.2, C109.2, C121.2, C122.2, C123.2, C124.2, C128.2, C129.2, J2.2 (Ext), J3.2 (Ext), R11.2, R16.1, R31.2, R36.1, U12.6 (V_{S-}), U13.6 (V_{S-}); also elsewhere on the board
VCMA: C109.1, U12.2 (V_{OCM}); also elsewhere on the board
VCMB: C129.1, U13.2 (V_{OCM}); also elsewhere on the board
